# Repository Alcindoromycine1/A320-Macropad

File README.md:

# A320-Macropad
A320 Style Speed/Heading Selector built with 2 rotary encoders, 2 pushbuttons, a status LED, and an OLED screen.firmware

# Features:
- 1x 0.9in OLED Display
- 2x EC11 Rotary encoder (One to control Speed, one to control HDG)
- 1x SK6812 Mini-e LEDs. It is a status light for the LOC button

# CAD Model:
This project was designed in Fusion 360 and is held together using M3 Screws and Heatset inserts.

It has 4 separate printed pieces. The base where the PCB is held, the lid, and two knobs to rotate the rotary encoders.
The knobs were used from Liam Egger's [project](https://www.printables.com/model/601969-autopilot-panel-fly-by-wire-a320neo/files) on printables.com

# PCB
Here's the PCB for this project. It was made in KiCad.

Schematic

PCB

I used the footprints and schematic parts from Hack Club's wesbite. The OLED screen could have been better modelled, but that is a problem for the future.

Firmware Overview
This hackpad, being a interface for a flight simulator, will use MobiFlight to interact with the simulator.

BOM:

- 2x Cherry MX Switches
- 2x DSA Keycaps
- 4x M3x5x4 Heatset inserts
- 4x M3x16mm  Bolts
- 1x SK6812 MINI-E LEDs
- 1x 0.91" 128x32 OLED Display
- 2x EC11 Rotary Encoder
- 1x XIAO RP2040
- 1x Case (4 printed parts)

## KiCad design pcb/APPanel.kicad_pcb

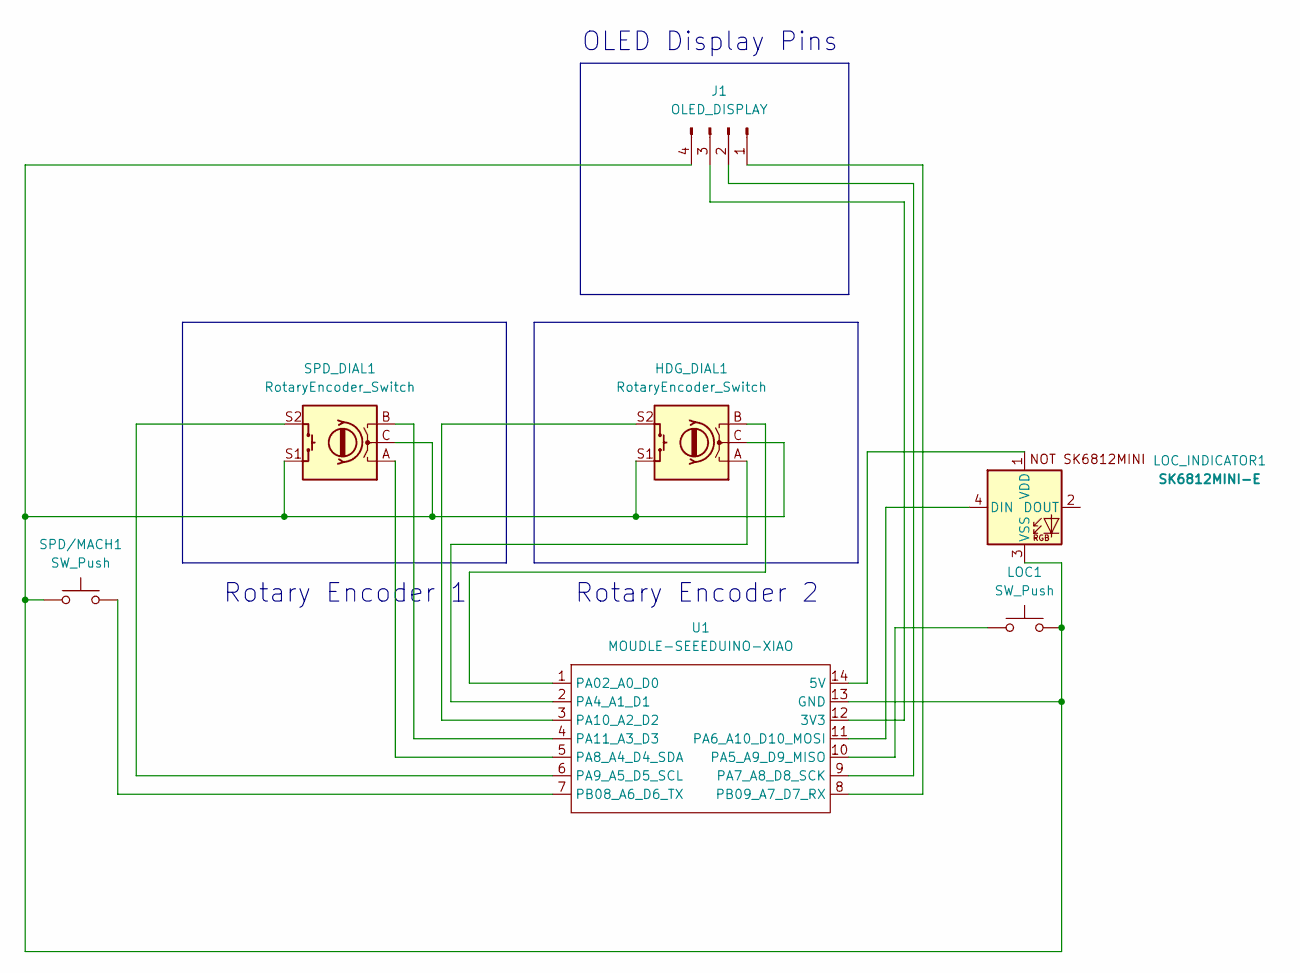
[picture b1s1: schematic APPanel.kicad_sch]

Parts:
HDG_DIAL1: RotaryEncoder_Switch; RotaryEncoder_Alps_EC11E-Switch_Vertical_H20mm
J1: OLED_DISPLAY; PinHeader_1x04_P2.54mm_Vertical
LOC1: SW_Push; SW_Cherry_MX_1.00u_PCB
LOC_INDICATOR1: SK6812MINI-E; SK6812MINI-E_fixed
SPD/MACH1: SW_Push; SW_Cherry_MX_1.00u_PCB
SPD_DIAL1: RotaryEncoder_Switch; RotaryEncoder_Alps_EC11E-Switch_Vertical_H20mm
U1: MOUDLE-SEEEDUINO-XIAO; XIAO-Generic-Hybrid-14P-2.54-21X17.8MM

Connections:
unnamed: J1.1, U1.8 (PB09_A7_D7_RX)
unnamed: J1.2, U1.9 (PA7_A8_D8_SCK)
unnamed: J1.3, U1.12 (3V3)
unnamed: HDG_DIAL1.C, HDG_DIAL1.S1, J1.4, LOC1.2, LOC_INDICATOR1.3 (VSS), SPD/MACH1.1, SPD_DIAL1.C, SPD_DIAL1.S1, U1.13 (GND)
unnamed: LOC_INDICATOR1.4 (DIN), U1.11 (PA6_A10_D10_MOSI)
unnamed: LOC_INDICATOR1.1 (VDD), U1.14 (5V)
unnamed: HDG_DIAL1.B, U1.1 (PA02_A0_D0)
unnamed: HDG_DIAL1.A, U1.2 (PA4_A1_D1)
unnamed: LOC1.1, U1.10 (PA5_A9_D9_MISO)
unnamed: SPD_DIAL1.A, U1.5 (PA8_A4_D4_SDA)
unnamed: SPD_DIAL1.S2, U1.6 (PA9_A5_D5_SCL)
unnamed: HDG_DIAL1.S2, U1.3 (PA10_A2_D2)
unnamed: SPD_DIAL1.B, U1.4 (PA11_A3_D3)
unnamed: SPD/MACH1.2, U1.7 (PB08_A6_D6_TX)

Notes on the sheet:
OLED Display Pins
Rotary Encoder 1
Rotary Encoder 2

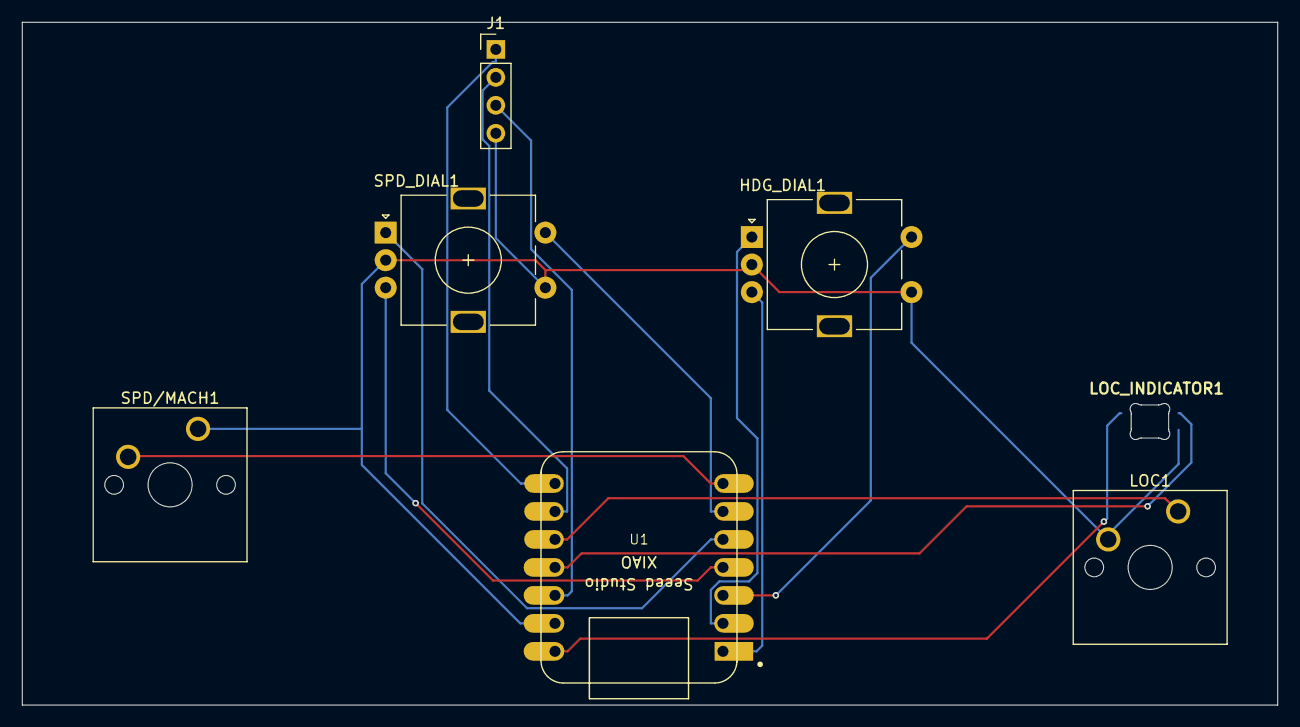
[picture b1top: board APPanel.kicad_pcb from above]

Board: 2 copper layers, 113.9 x 62.0 mm, 7 parts (0 on the bottom side), 14 nets.

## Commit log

2026-06-30 Rename Screenshot 2026-06-30 123249.png to assets/schematic.png
2026-06-30 Rename Screenshot 2026-06-30 123521.png to assets/cad_nolid.png
2026-06-30 Rename Screenshot 2026-06-30 123526.png to assets/cad.png
2026-06-30 Rename Screenshot 2026-06-30 123545.png to assets/pcb.png
2026-06-30 Rename image.png to knobs.png
2026-06-30 Create test
2026-06-30 Create temp
